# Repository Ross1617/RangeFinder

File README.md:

# RangeFinder
Link to video of the prototype in action https://www.youtube.com/shorts/F2ILh-BwJkE

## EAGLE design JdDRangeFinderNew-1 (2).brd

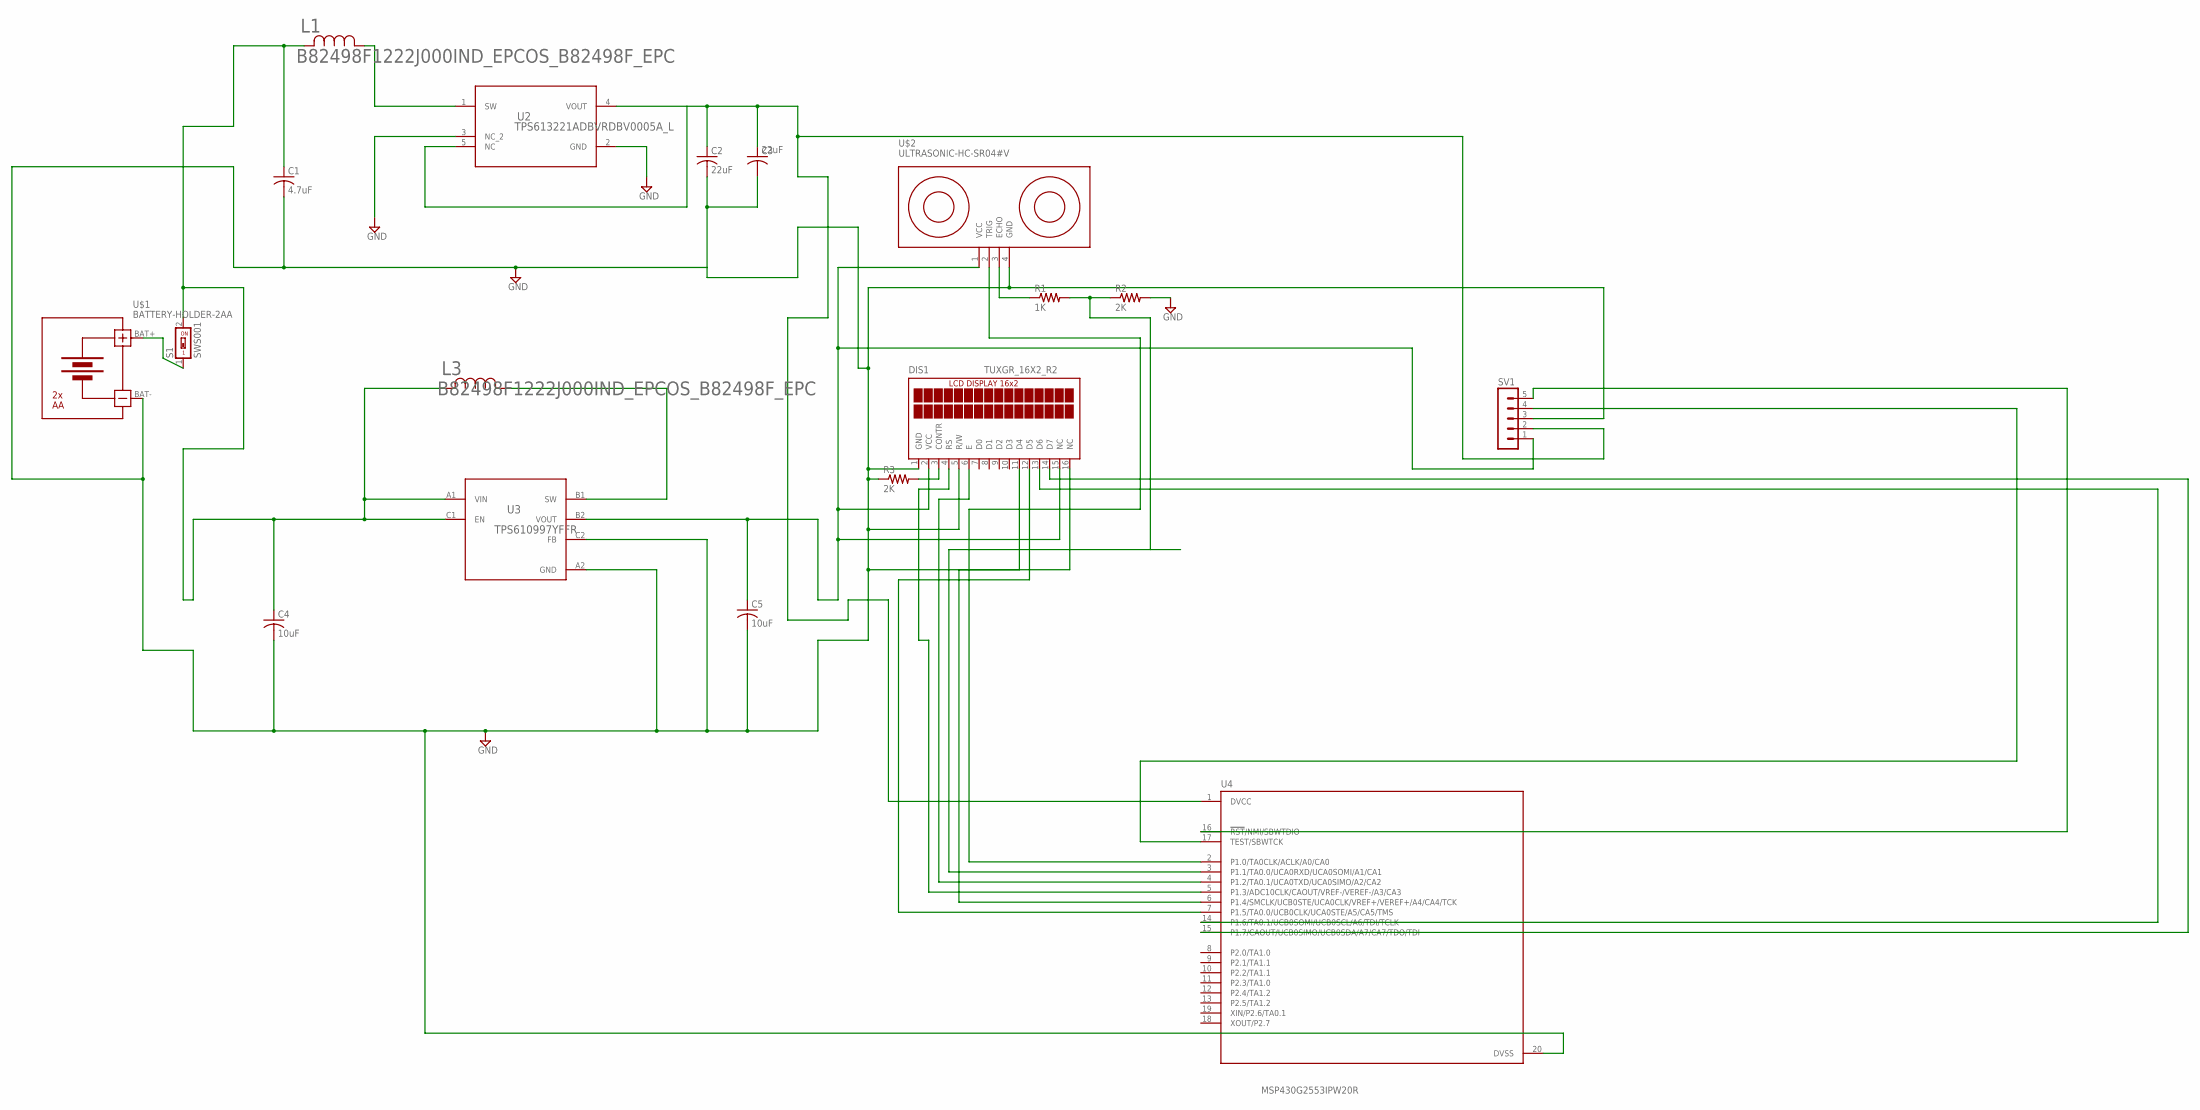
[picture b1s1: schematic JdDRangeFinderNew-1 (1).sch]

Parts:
C1: 4.7uF; C0805
C2, C3: 22uF; C0805
C4, C5: 10uF; C0805
DIS1: TUXGR_16X2_R2
L1, L3: B82498F1222J000IND_EPCOS_B82498F_EPC; IND_EPCOS_B82498F_EPC
R1: 1K; R0805
R2, R3: 2K; R0805
S1: SWS001; SMS-001
SV1: MA05-1
U2: TPS613221ADBVRDBV0005A_L; DBV0005A_L
U3: TPS610997YFFR; YFF0006AFAD
U4: MSP430G2553IPW20R; SOP65P640X120-20N
U$1: BATTERY-HOLDER-2AA
U$2: ULTRASONIC-HC-SR04#V

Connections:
GND: C1.2, C2.2, C3.2, C4.2, C5.2, DIS1.1 (GND), DIS1.5 (R/W), DIS1.16 (NC), R2.2, R3.1, SV1.3, U2.2 (GND), U2.3 (NC_2), U3.A2 (GND), U3.C2 (FB), U4.20 (DVSS), U$1.BAT-, U$2.4 (GND)
unnamed: SV1.4, U4.17 (TEST/SBWTCK)
unnamed: C2.1, C3.1, SV1.2, U2.4 (VOUT), U2.5 (NC), U4.1 (DVCC)
unnamed: L3.1, U3.B1 (SW)
unnamed: C5.1, DIS1.2 (VCC), DIS1.15 (NC), SV1.1, U3.B2 (VOUT), U$2.1 (VCC)
unnamed: U4.2 (P1.0/TA0CLK/ACLK/A0/CA0), U$2.2 (TRIG)
unnamed: R1.1, U$2.3 (ECHO)
unnamed: C1.1, C4.1, L1.2, L3.2, S1.2, U3.A1 (VIN), U3.C1 (EN)
unnamed: L1.1, U2.1 (SW)
unnamed: DIS1.4 (RS), U4.5 (P1.3/ADC10CLK/CAOUT/VREF-/VEREF-/A3/CA3)
unnamed: DIS1.6 (E), U4.4 (P1.2/TA0.1/UCA0TXD/UCA0SIMO/A2/CA2)
unnamed: DIS1.11 (D4), U4.6 (P1.4/SMCLK/UCB0STE/UCA0CLK/VREF+/VEREF+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)
unnamed: DIS1.12 (D5), U4.7 (P1.5/TA0.0/UCB0CLK/UCA0STE/A5/CA5/TMS)
unnamed: DIS1.13 (D6), U4.14 (P1.6/TA0.1/UCB0SOMI/UCB0SCL/A6/TDI/TCLK)
unnamed: DIS1.14 (D7), U4.15 (P1.7/CAOUT/UCB0SIMO/UCB0SDA/A7/CA7/TDO/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)
unnamed: DIS1.3 (CONTR), R3.2
unnamed: S1.1, U$1.BAT+
unnamed: SV1.5, U4.16 (!RST!/NMI/SBWTDIO)
unnamed: R1.2, R2.1, U4.3 (P1.1/TA0.0/UCA0RXD/UCA0SOMI/A1/CA1)

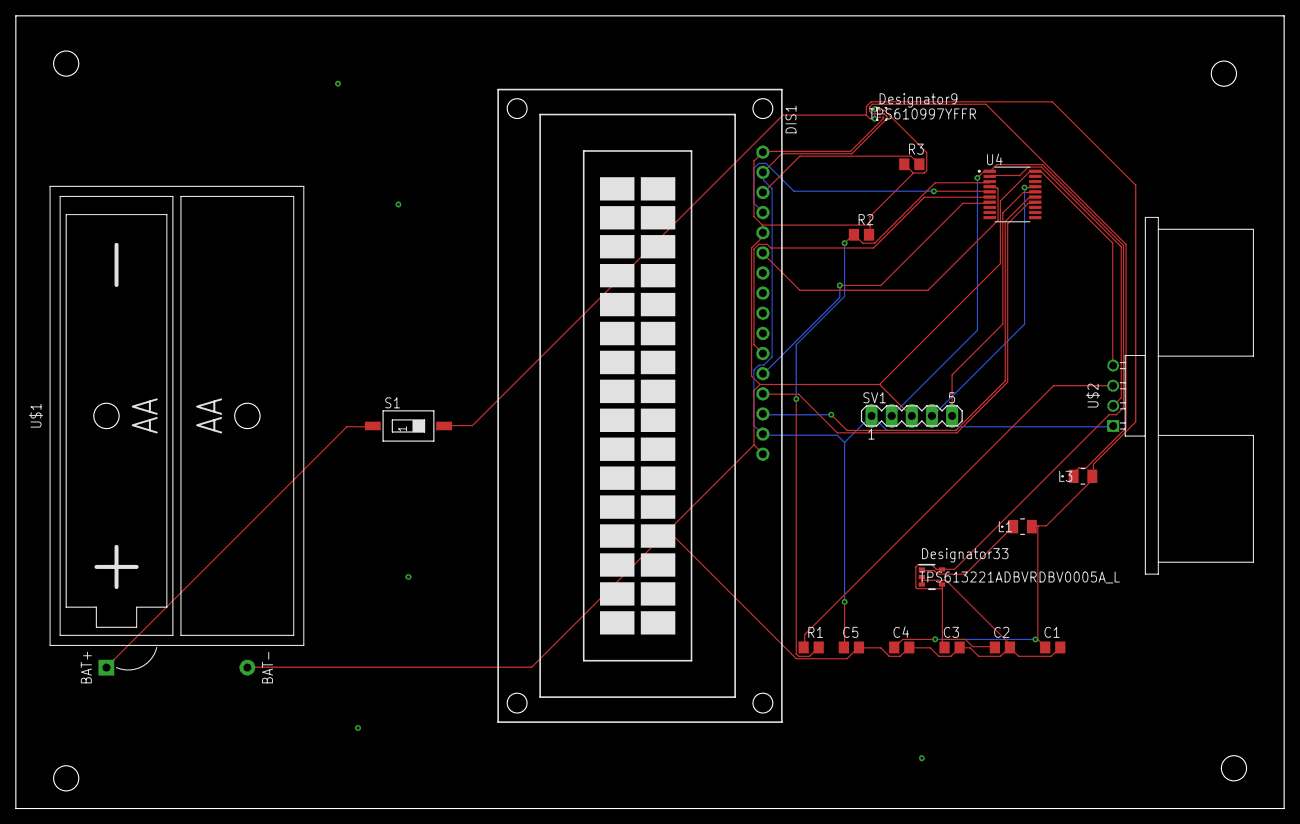
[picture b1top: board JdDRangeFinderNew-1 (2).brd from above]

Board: 2 copper layers, 160.0 x 100.0 mm, 18 parts (0 on the bottom side), 19 nets.

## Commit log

2022-11-15 Create Prototype In Use

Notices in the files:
parts and their libraries:
3.3: COPYRIGHT: Copyright (C) 2022 Ultra Librarian. All rights reserved.
6 diy-modules: Released under the Creative Commons Attribution 4.0 International License: http://creativecommons.org/licenses/by/4.0
